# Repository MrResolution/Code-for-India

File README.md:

# 🤖🦾 Robotics Integrated Control Center & Multi-Robot Simulation

A unified robotics engineering platform featuring a **Multi-DOF Robotic Arm with a parallel geared gripper**, an **8-servo Sesame Quadruped Robot ("Quard Bot")**, an **ESP32 Rover Telemetry Node**, **Dogu** (a 12-servo robot dog you can start and stop over Wi-Fi, with a 3D model preview), and an **interactive PyQt5 Dashboard** with side-by-side **embedded native RViz2 3D visualization** and **Three.js WebGL digital twins**.

---

## ⚡ Quick Launch

From the project root directory:

```bash
# 🤖 Launch Quard Bot (Quadruped) in Dashboard + Embedded RViz2
./launch_quard_dashboard.sh

# 🦾 Launch 6-DOF Robotic Arm in Dashboard + Embedded RViz2
./launch_dashboard.sh

# ⚡ Launch Dual Robots (Arm + Quadruped simultaneously in RViz2)
./launch_dual_dashboard.sh

# 🐕 Launch Dogu (12-joint quadruped model preview + animations) in RViz2
./launch_dogu_dashboard.sh

# 🌐 Launch Standalone WebGL 3D Dashboard (Browser: http://localhost:8000)
./launch_web_dashboard.sh                  # add --host 0.0.0.0 for phones/tablets (no auth!)
```

> ⛔ **E-STOP:** both dashboards have an E-STOP button in the header (or press **Esc**). It stops all dashboard-driven motion and locks the controls. It is a software stop and does not cut servo power. See [Safety Controls](docs/DASHBOARD_AND_RVIZ_GUIDE.md#-5-safety-controls).

> 🗺️ **New to the repo (human or AI agent)?** Start with [PROJECT_MAP.md](PROJECT_MAP.md): where everything lives, how the pieces talk, and the pitfalls.

> **First time running?** See the [🛠️ Quick Installation Guide](docs/QUICK_INSTALL_GUIDE.md) to set up ROS 2 Jazzy, RViz2, and `xdotool` in under 3 minutes.

---

## 🏗️ System Highlights

- **Embedded Native RViz2**: Seamlessly docked into the desktop dashboard frame via X11 reparenting with strict PID and window-class isolation.
- **Web Dashboard**: Three.js twin at `http://localhost:8000`.
  - Light and dark themes; works at phone width.
  - Live status badges for the ROS bridge, Quard Bot and sensor node.
  - Runs UI-only without ROS 2.
- **Connections & consoles** (every tab, both UIs):
  - Live link state with the reason when something is wrong, ping round trip, ⟳ Reconnect, and port / IP changes without a restart.
  - Consoles with colour, filter, find, pause, copy, save and command history; raw commands to the arm ESP32 or the Quard Bot.
- **Safety**:
  - E-STOP (button or **Esc**) in both UIs.
  - The Quard firmware's 2 s locomotion watchdog is honoured: the active gait is resent every second.
- **Quard Bot Quadruped Control**:
  - D-Pad & keyboard locomotion (WASD / Space) with 4-phase gait trajectory generation.
  - Quick stance presets (`Stand 45°`, `Base Zero 0°`, `Crouch 30°`, `High 60°`, `Wave`).
  - PCA9685 8-channel live servo slider management.
- **Robotic Arm Control**:
  - Joint angle sliders with real-time degree and radian readouts.
  - "📍 Set Low" and "📍 Set High" safety boundary calibration (the web UI shows the saved range on each slider).
  - Smooth homing (`🏠 Go Home`), `📌 Set Home`, and automated sinusoidal motion simulation.
  - Save calibration with `💾 Save Config` or Ctrl+S (desktop).
- **Dogu (robot dog)**:
  - Firmware `src/dogu.cpp` (ESP32 + PCA9685): walks with 8 servos, holds 4 body servos, starts its own Wi-Fi access point. See [docs/DOGU.md](docs/DOGU.md).
  - Its tab in both UIs connects to `http://192.168.4.1`: live status (walking, leg, phase) with **Start walking** / **Stop walking**; E-STOP sends Stop.
  - Its own tab in both UIs: Stand / Crouch / Sit poses and Walk, Turn, Wave and Idle animations, with a speed slider and live joint angles.
  - The model is built from `cad/dogu/Dogu.blend` by `scripts/dogu/`. Its poses and animations move the 3D model only.
- **Rover Telemetry & Sensors**:
  - Climate: DHT11 & BMP280 temperature, humidity, and barometric pressure.
  - Hazards: MQ Gas, water level, and optical flame detector with emergency fire alerts.
  - Motion: 6-DOF MPU6050 IMU accelerometer, gyroscope, and pitch/roll tilt.
  - Navigation: NEO-6M GPS coordinates and satellite lock telemetry.

---

## 📂 Project Structure

The full map, with "where do I find X" tables, data flow, topics, ports and pitfalls, is in **[PROJECT_MAP.md](PROJECT_MAP.md)**.

```text
.
├── launch_*.sh            # One-click launchers (dashboard, quard, dual, dogu, web, gesture teleop)
├── run_all.sh             # Older all-in-one launcher (sim / real menu)
├── servo_calibration.json # Arm calibration, read and written by both dashboards
├── ros2_ws/               # ROS 2 package servo_joint_publisher: dashboards, commanders, web twin
├── urdf/                  # Runtime robot models used by RViz and the web twin
│   ├── arm/  quard_bot/  dogu/  dual_robots.urdf
│   └── unnamed/           # Arm launch file (display_ros2.launch.py), sim + legacy Gazebo tools
├── src/  include/  lib/   # ESP32 / ESP8266 firmware (PlatformIO; envs in platformio.ini)
├── scripts/               # Model build tools (Dogu export/build, Quard/arm URDF generator, 3MF→STL)
├── cad/                   # Source CAD: Blender scenes and printable STLs (not loaded at runtime)
├── hardware/              # Carrier PCB (KiCad, Gerbers) and the BTS7960 motor controller
└── docs/                  # Guides, Quard Bot manual, project context, presentation, diagrams
```

---

## 🦾 Kinematic Architecture

### 1. 6-DOF Robotic Arm & Parallel Gripper

| Joint Name | Type | Axis | Physical Function |
|---|---|---|---|
| `turntable_link_joint_dup` | Revolute | Z | Base Turntable Yaw (±180°) |
| `turntable_link_joint` | Revolute | Y | Shoulder Pitch (Dual Servos: GPIO 19 & 21) |
| `turntable_link_joint_dup_1` | Revolute | Y | Elbow 1 Pitch |
| `turntable_link_joint_dup_2` | Revolute | Y | Elbow 2 Pitch |
| `turntable_link_joint_dup_3` | Revolute | Z | Wrist Twist / Roll (GPIO 27) |
| `grip` | Revolute | Z | Geared Parallel Gripper (GPIO 26) |
| `mimic ×5` | Mimic | — | 4-bar parallel follower links & opposing gear |

### 2. Sesame Quadruped ("Quard Bot")

| PCA9685 Channel | Leg Location | Joint Role | Neutral |
|---|---|---|---|
| **Ch 0** | Right Front (R1) | Hip Joint | 45° |
| **Ch 1** | Right Rear (R2)  | Hip Joint | 45° |
| **Ch 2** | Left Rear (L2)   | Hip Joint | 45° |
| **Ch 3** | Left Front (L1)  | Hip Joint | 45° |
| **Ch 4** | Right Front (R3) | Knee Joint | 45° |
| **Ch 5** | Right Rear (R4)  | Knee Joint | 45° |
| **Ch 6** | Left Rear (L4)   | Knee Joint | 45° |
| **Ch 7** | Left Front (L3)  | Knee Joint | 45° |

### 3. Dogu (12-joint quadruped, model preview)

| Joints | Legs | Role | Zero |
|---|---|---|---|
| `{fl,fr,bl,br}_hip_joint` | front/back × left/right | Abduction (leg out to the side) | Standing |
| `{fl,fr,bl,br}_femur_joint` | | Upper leg pitch | Standing |
| `{fl,fr,bl,br}_tibia_joint` | | Knee | Standing |

Every joint turns about its own z axis and reads 0 in the standing pose. The ±90° limits are provisional until the servo mapping is confirmed. The firmware's own servo channels are in [docs/DOGU.md](docs/DOGU.md).

---

## 📚 Documentation Reference

- **[Project Map](PROJECT_MAP.md)**: directory map, where to find things, data flow, topics, ports and pitfalls. Start here.
- **[Agent Guide](AGENTS.md)**: rules and checks for AI coding agents (and humans) changing this repo.
- **[Quick Installation Guide](docs/QUICK_INSTALL_GUIDE.md)**: ROS 2 Jazzy, RViz2, and `xdotool` setup.
- **[Dashboard & RViz Docking Guide](docs/DASHBOARD_AND_RVIZ_GUIDE.md)**: Both UIs, control panels, connections & consoles, E-STOP and safety, keyboard shortcuts, web dashboard options, troubleshooting.
- **[Project Context & Handoff](docs/PROJECT_CONTEXT.md)**: Phobos patch details, gripper mimic joint math, and developer notes.
- **[Quard Bot Firmware & Hardware](docs/QUARD_BOT.md)**: Pinouts, OLED animations, Web AP instructions and the HTTP API.
- **[Dogu robot](docs/DOGU.md)**: hardware, servo channels, Wi-Fi access point, HTTP API and safety.
- **[Dogu model](urdf/dogu/README.md)**: how the Dogu URDF and animations are built from the Blender scene.
- **[Robotic Arm Carrier PCB](hardware/robotic_arm_motherboard/README.md)**: Custom KiCad carrier board and Gerbers.
- **[CAD sources](cad/README.md)**: Blender scenes and printable STLs for every robot.
- **[Project Presentation](docs/PROJECT_PRESENTATION.md)**: the long-form project write-up.

---

## 📄 License

This project is open-source under standard robotics educational licenses. See individual component directories for specific asset licensing.

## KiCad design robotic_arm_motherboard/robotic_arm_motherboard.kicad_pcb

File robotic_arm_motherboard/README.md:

# 🦾 5-DOF Robotic Arm Modular Carrier Motherboard

> **Carrier PCB & Backplane** · KiCad 7 / 8 · ESP32 DevKit V1 Socket · PCA9685 Module Socket · Dual VL53L1X ToF · XT30 Power

A professional 100mm × 80mm 2-layer FR4 carrier / motherboard PCB designed to interconnect the electronic modules of the 5-DOF robotic arm without hard-soldering microcontrollers or driver ICs. All commercial off-the-shelf (COTS) modules plug directly into standard 2.54mm female pin headers.

---

## 📐 Board Overview & Specifications

| Parameter | Specification |
| :--- | :--- |
| **Dimensions** | 100.0 mm × 80.0 mm |
| **Layers** | 2-layer FR4, 1.6 mm thickness, 1 oz copper ($35\,\mu\text{m}$) |
| **Surface Finish** | HASL Lead-Free (or ENIG) |
| **Mounting Holes** | 4× M3 mounting holes at corners with 3.5 mm edge inset (93.0 mm × 73.0 mm spacing) |
| **Power Input** | XT30 connector (SERVO_V+: 5.0V – 6.0V external DC, 5A–10A capability) |
| **Protection** | 5A mini blade/SMD fuse (F1) + Schottky reverse polarity diode (D1) + 1000 µF low-ESR bulk electrolytic capacitor (C1) |
| **Logic Supply** | Onboard AMS1117-3.3 LDO regulator providing clean 3.3V rail from servo power |
| **Signal Integrity** | Ground planes on bottom layer, wide 2.0 mm power distribution traces, localized 0.1 µF & 10 µF decoupling |

---

## 🧩 Modular Socket Architecture

### 1. ESP32 DevKit V1 Socket
* Dual 1×15 female socket headers spaced **22.86 mm (0.9")** apart with standard 2.54 mm pitch.
* Sockets accept any standard 30-pin ESP32 DevKit V1 board.
* Dedicated antenna keepout zone ensuring zero Wi-Fi / Bluetooth attenuation.
* Dedicated breakout lines for I2C (GPIO21 SDA, GPIO22 SCL), UART (TX0, RX0), and ToF sensor shutdown (GPIO16 XSHUT1, GPIO17 XSHUT2).

### 2. PCA9685 16-Channel Servo Driver Module Socket & Mount
* **Direct Servo Connection**: RC servos (MG996R, SG90, DS3218, etc.) plug **directly** into the PCA9685 module's native 16×3 male header pins. No duplicate servo headers on the carrier motherboard.
* Module connects to the motherboard via a 6-pin control header: `GND`, `OE` (Active-Low Output Enable), `SCL`, `SDA`, `VCC` (3.3V), and `V+` (Servo Power).
* Accompanied by a custom 3D-printable elevated mounting bracket (`pca9685_mount_bracket.stl` and `pca9685_mount_bracket.scad`) that secures the module cleanly above the PCB.

### 3. Dual VL53L1X Time-of-Flight (ToF) Distance Sensors
* 2× 5-pin headers (`J_VL53_1`, `J_VL53_2`): `3V3`, `GND`, `SDA`, `SCL`, `XSHUT`.
* Allows dynamic I2C address reassignment at boot for dual-sensor LiDAR and obstacle ranging.

### 4. Expansion & Debug Headers
* **I2C Expansion (J_I2C_EXP)**: 4-pin (`3V3`, `GND`, `SDA`, `SCL`) with 4.7 kΩ pull-ups.
* **UART Debug (J_UART)**: 4-pin (`3V3`, `GND`, `TX`, `RX`).
* **GPIO Breakout (J_GPIO_EXP)**: 10-pin header exposing spare ESP32 GPIOs for limit switches, encoders, or buttons.
* **Safety Controls**: Emergency Stop 2-pin header (`J_ESTOP`) and hardware Servo Enable 2-pin header (`J_SRV_EN`).
* **Status LEDs**: 3.3V Power (LED1), Servo V+ Active (LED2), Arm Status (LED3), Fault/Disable (LED4).

---

## 📁 Included Files

* **KiCad Design Files**:
  * `robotic_arm_motherboard.kicad_pcb`: PCB layout (tracks, pours, footprints, silkscreen).
  * `robotic_arm_motherboard.kicad_sch`: Schematic with power, sockets, protection, and decoupling.
  * `robotic_arm_motherboard.kicad_pro`: KiCad 7/8 project configuration.
* **Fabrication & Assembly**:
  * `robotic_arm_motherboard_gerbers.zip`: Ready-to-upload ZIP for JLCPCB, PCBWay, or OSH Park.
  * `production_gerbers/`: Individual RS-274X Gerber layers and Excellon NC drill files.
  * `BOM.csv`: Complete bill of materials with references, values, and footprints.
  * `robotic_arm_motherboard-pos.csv`: Component pick-and-place centroid positions.
  * `robotic_arm_motherboard-pcb.pdf`: High-resolution vector schematic and layer plots.
* **3D Models**:
  * `robotic_arm_motherboard-3d.step`: Full 3D CAD model of the carrier board.
  * `pca9685_mount_bracket.stl`: 3D printable bracket for the PCA9685 module.
  * `pca9685_mount_bracket.scad`: Parametric OpenSCAD source file.
* **Visuals**:
  * `pcb_layout_diagram.svg`: Dimensioned topology and socket arrangement diagram.
  * `pcb_render.svg`: Top layer vector render.

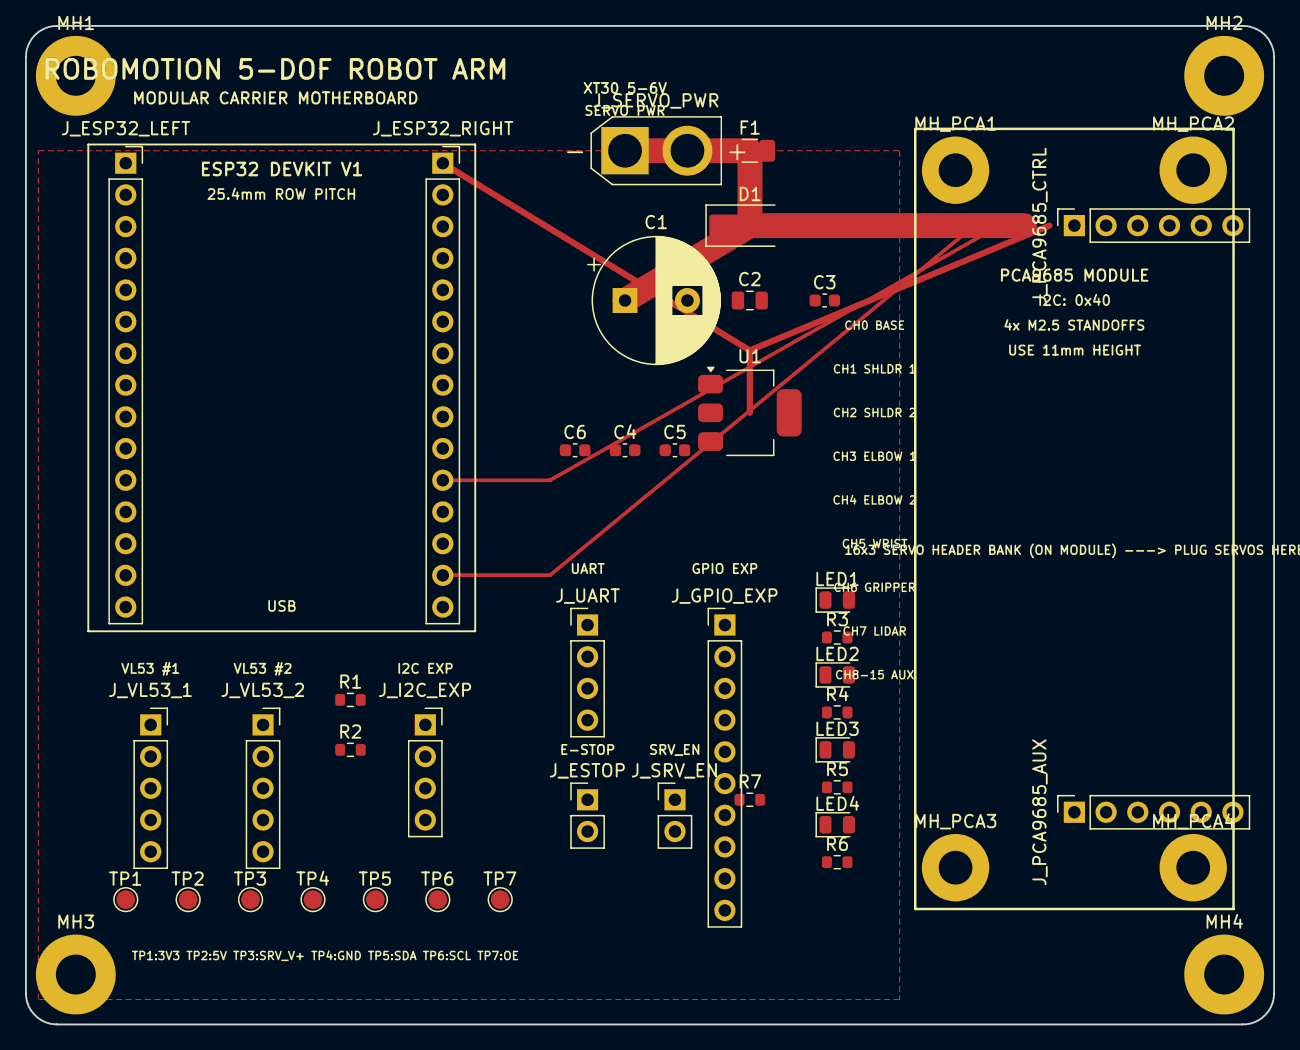
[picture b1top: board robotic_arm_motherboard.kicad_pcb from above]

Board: 2 copper layers, 100.0 x 80.0 mm, 47 parts (0 on the bottom side), 19 nets.

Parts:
C1: CP_Radial_D10.0mm_P5.00mm
C2: C_0805_2012Metric
C3, C4, C5, C6: C_0603_1608Metric
D1: D_SMA
F1: Fuse_1206_3216Metric
J_ESP32_LEFT, J_ESP32_RIGHT: PinSocket_1x15_P2.54mm_Vertical
J_ESTOP: PinHeader_1x02_P2.54mm_Vertical
J_GPIO_EXP: PinHeader_1x10_P2.54mm_Vertical
J_I2C_EXP: PinSocket_1x04_P2.54mm_Vertical
J_PCA9685_AUX, J_PCA9685_CTRL: PinSocket_1x06_P2.54mm_Vertical
J_SERVO_PWR: AMASS_XT30U-F_1x02_P5.0mm_Vertical
J_SRV_EN: PinHeader_1x02_P2.54mm_Vertical
J_UART: PinHeader_1x04_P2.54mm_Vertical
J_VL53_1, J_VL53_2: PinSocket_1x05_P2.54mm_Vertical
LED1, LED2, LED3, LED4: LED_0805_2012Metric
MH1, MH2, MH3, MH4: MountingHole_3.2mm_M3_Pad
MH_PCA1, MH_PCA2, MH_PCA3, MH_PCA4: MountingHole_2.7mm_M2.5_Pad
R1, R2, R3, R4, R5, R6, R7: R_0603_1608Metric
TP1, TP2, TP3, TP4, TP5, TP6, TP7: TestPoint_Pad_D1.5mm
U1: SOT-223-3_TabPin2

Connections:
5V_LOGIC: J_ESP32_RIGHT.1, TP2.1
+3V3: C4.1, C5.1, C6.1, J_ESP32_LEFT.1, J_GPIO_EXP.9, J_I2C_EXP.1, J_PCA9685_AUX.5, J_PCA9685_CTRL.5, J_UART.1, J_VL53_1.1, J_VL53_2.1, LED1.1, LED3.1, R1.1, R2.1, R7.1, TP1.1, U1.2
GND: C1.2, C2.2, C3.2, C4.2, C5.2, C6.2, D1.1, J_ESP32_LEFT.14, J_ESP32_RIGHT.2, J_ESTOP.2, J_GPIO_EXP.10, J_I2C_EXP.2, J_PCA9685_AUX.1, J_PCA9685_CTRL.1, J_SERVO_PWR.2, J_SRV_EN.2, J_UART.2, J_VL53_1.2, J_VL53_2.2, LED1.2, LED2.2, LED3.2, LED4.2, MH1.1, MH2.1, MH3.1, MH4.1, MH_PCA1.1, MH_PCA2.1, MH_PCA3.1, MH_PCA4.1, TP4.1, U1.1
GPIO12: J_ESP32_LEFT.13, J_GPIO_EXP.7
GPIO13: J_ESP32_LEFT.15, J_GPIO_EXP.8
GPIO14: J_ESP32_LEFT.12, J_GPIO_EXP.6
GPIO25: J_ESP32_LEFT.9, J_GPIO_EXP.3
GPIO26: J_ESP32_LEFT.10, J_GPIO_EXP.4
GPIO27: J_ESP32_LEFT.11, J_GPIO_EXP.5
GPIO32: J_ESP32_LEFT.7, J_GPIO_EXP.1
GPIO33: J_ESP32_LEFT.8, J_GPIO_EXP.2
OE: J_PCA9685_AUX.2, J_PCA9685_CTRL.2, LED4.1, R7.2, TP7.1
SCL: J_ESP32_RIGHT.14, J_I2C_EXP.4, J_PCA9685_AUX.3, J_PCA9685_CTRL.3, J_VL53_1.4, J_VL53_2.4, R2.2, TP6.1
SDA: J_ESP32_RIGHT.11, J_I2C_EXP.3, J_PCA9685_AUX.4, J_PCA9685_CTRL.4, J_VL53_1.3, J_VL53_2.3, R1.2, TP5.1
SERVO_V+: C1.1, C2.1, C3.1, D1.2, F1.1, F1.2, J_PCA9685_AUX.6, J_PCA9685_CTRL.6, J_SERVO_PWR.1, LED2.1, TP3.1, U1.3
UART_RX: J_ESP32_RIGHT.12, J_UART.4
UART_TX: J_ESP32_RIGHT.13, J_UART.3
XSHUT1: J_ESP32_RIGHT.6, J_VL53_1.5
XSHUT2: J_ESP32_RIGHT.7, J_VL53_2.5

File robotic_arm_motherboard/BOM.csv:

Reference,Value,Footprint,Quantity,Description
"C1","C_Polarized","",1,""
"C2 C3 C4 C5 C6","C","",5,""
"D1","D_Schottky","",1,""
"F1","Fuse","",1,""
"J_ESP32_LEFT J_ESP32_RIGHT","Conn_01x15","",2,""
"J_ESTOP J_SERVO_PWR J_SRV_EN","Conn_01x02","",3,""
"J_GPIO_EXP","Conn_01x10","",1,""
"J_I2C_EXP J_UART","Conn_01x04","",2,""
"J_PCA9685_CTRL","Conn_01x06","",1,""
"J_VL53_1 J_VL53_2","Conn_01x05","",2,""
"LED1 LED2 LED3 LED4","LED","",4,""
"R1 R2 R3 R4 R5 R6 R7","R","",7,""
"TP1 TP2 TP3 TP4 TP5 TP6 TP7","TestPoint","",7,""
"U1","AMS1117-3.3","",1,""

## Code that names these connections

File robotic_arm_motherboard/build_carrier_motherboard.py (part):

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    assign_net(mh, "1", "GND")

# ESP32 LEFT row
esp_l_nets = ["+3V3", "", "", "", "", "", "GPIO32", "GPIO33", "GPIO25", "GPIO26", "GPIO27", "GPIO14", "GPIO12", "GND", "GPIO13"]
for p, n in enumerate(esp_l_nets, 1):
    if n: assign_net("J_ESP32_LEFT", p, n)

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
